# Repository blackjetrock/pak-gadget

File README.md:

# pak-gadget
Psion Organiser II datapak replacement using RP2040

Code for a replacement Psion datapak that uses the RP2040 to create a datapak image that is interfaced using one of the datapak slots in the Organiser.
The gadget has an SD slot that can hold .opk files which are presented to the organiser as a datapak. There's a small OLED display and buttons so the image can be selected. The pak gadget can also present a rampak and data can be stored on the ram pak. That can then be saved to SD card using the menu system.
Power is USB as the datapak interface does not have a permanent power supply.

There are two versions:

Breakout pak-gadget
===================

A 'breakout' pak-gadget which is a T shaped PCB that plugs in to the datapak slot and has the display and buttons facing forwards. This is quite large.

Pak Sized pak-gadget
====================

This is a pak-gadget that fits in the form factor of a datapak in the slot in the organiser. It has a smaller OLED display and buttons that both face towards the back of the organiser. Power is still USB. When disconnected from power the organiser cover should fit in the closed position. The gadget can be wired in to the internal power supply of the organiser.On older PCB designs this requires an external transistor and a wire to the gadget. The later designs have that on the gadget PCB and require two wires.

Operation
=========

The pak gadget plugs in to either datapack slot on a Psion Organiser 2. It can be powered by the USB socket on the PCB, or it can be wired in to the 
internal supply of the organiser. A transistor is needed to switch the battery voltage on to the gadget when the LCD controller is turned on. When wired in 
the USB connection MUST NOT be used. A later revision of the PCB (untested as yet) has the extra transistor needed for internal power on the PCB.

The gadget runs in a tight loop when emulating a datapack in order to operate at the speeds needed to interact with the Psion, which means it cannot handle a 
menu while emulating.

There are four buttons on the gadget. The left most button breaks the gadget out of its tight loop and starts a menu. UP and DOWN are the rightmost two 
buttons. The button second from left is an OK button.

The code reads a file called config.txt from the SD card when it starts up. At the moment this just sets the .OPK image that will initially be used.
pack header bytes are passed through from the OPk file to the organiser unchanged, apart from the size byte. The pak gadget can only support pack images up to 
and including 128K so the size byte is altered to be no larger than 128K.

Menu options
============

List
----
This lists the .OPK files on the SD card. Selecting a file loads it into the gadget RAM buffer ready to emulate it when the menu is exited.

Write
-----
This writes the current RAM data to a file on the SD card. This enables a pak gadget that has been used as a RAM pack to save the data on SD card so that 
it can be loaded back in later. When power is removed the RAM b uffer is lost so this is the only way to have non volatile storage with the pak gadget.

The files are written with the name:
paknnnnn.opk

where nnnnn is an increasing number for each file saved. The pak gadget checks for the last nnnnn used by a file on the SD card and picks the next 
highest number for each file write.

Blank
-----
This clears the RAM buffer and sets the pak gadget up as a blank pack which can then be sized and used as a RAM pack.

Exit
----
This exits the menu and enters the emulation loop so that the pak gadget will look like a datapack again. While in the menu system the gadget does not emulate a pack.

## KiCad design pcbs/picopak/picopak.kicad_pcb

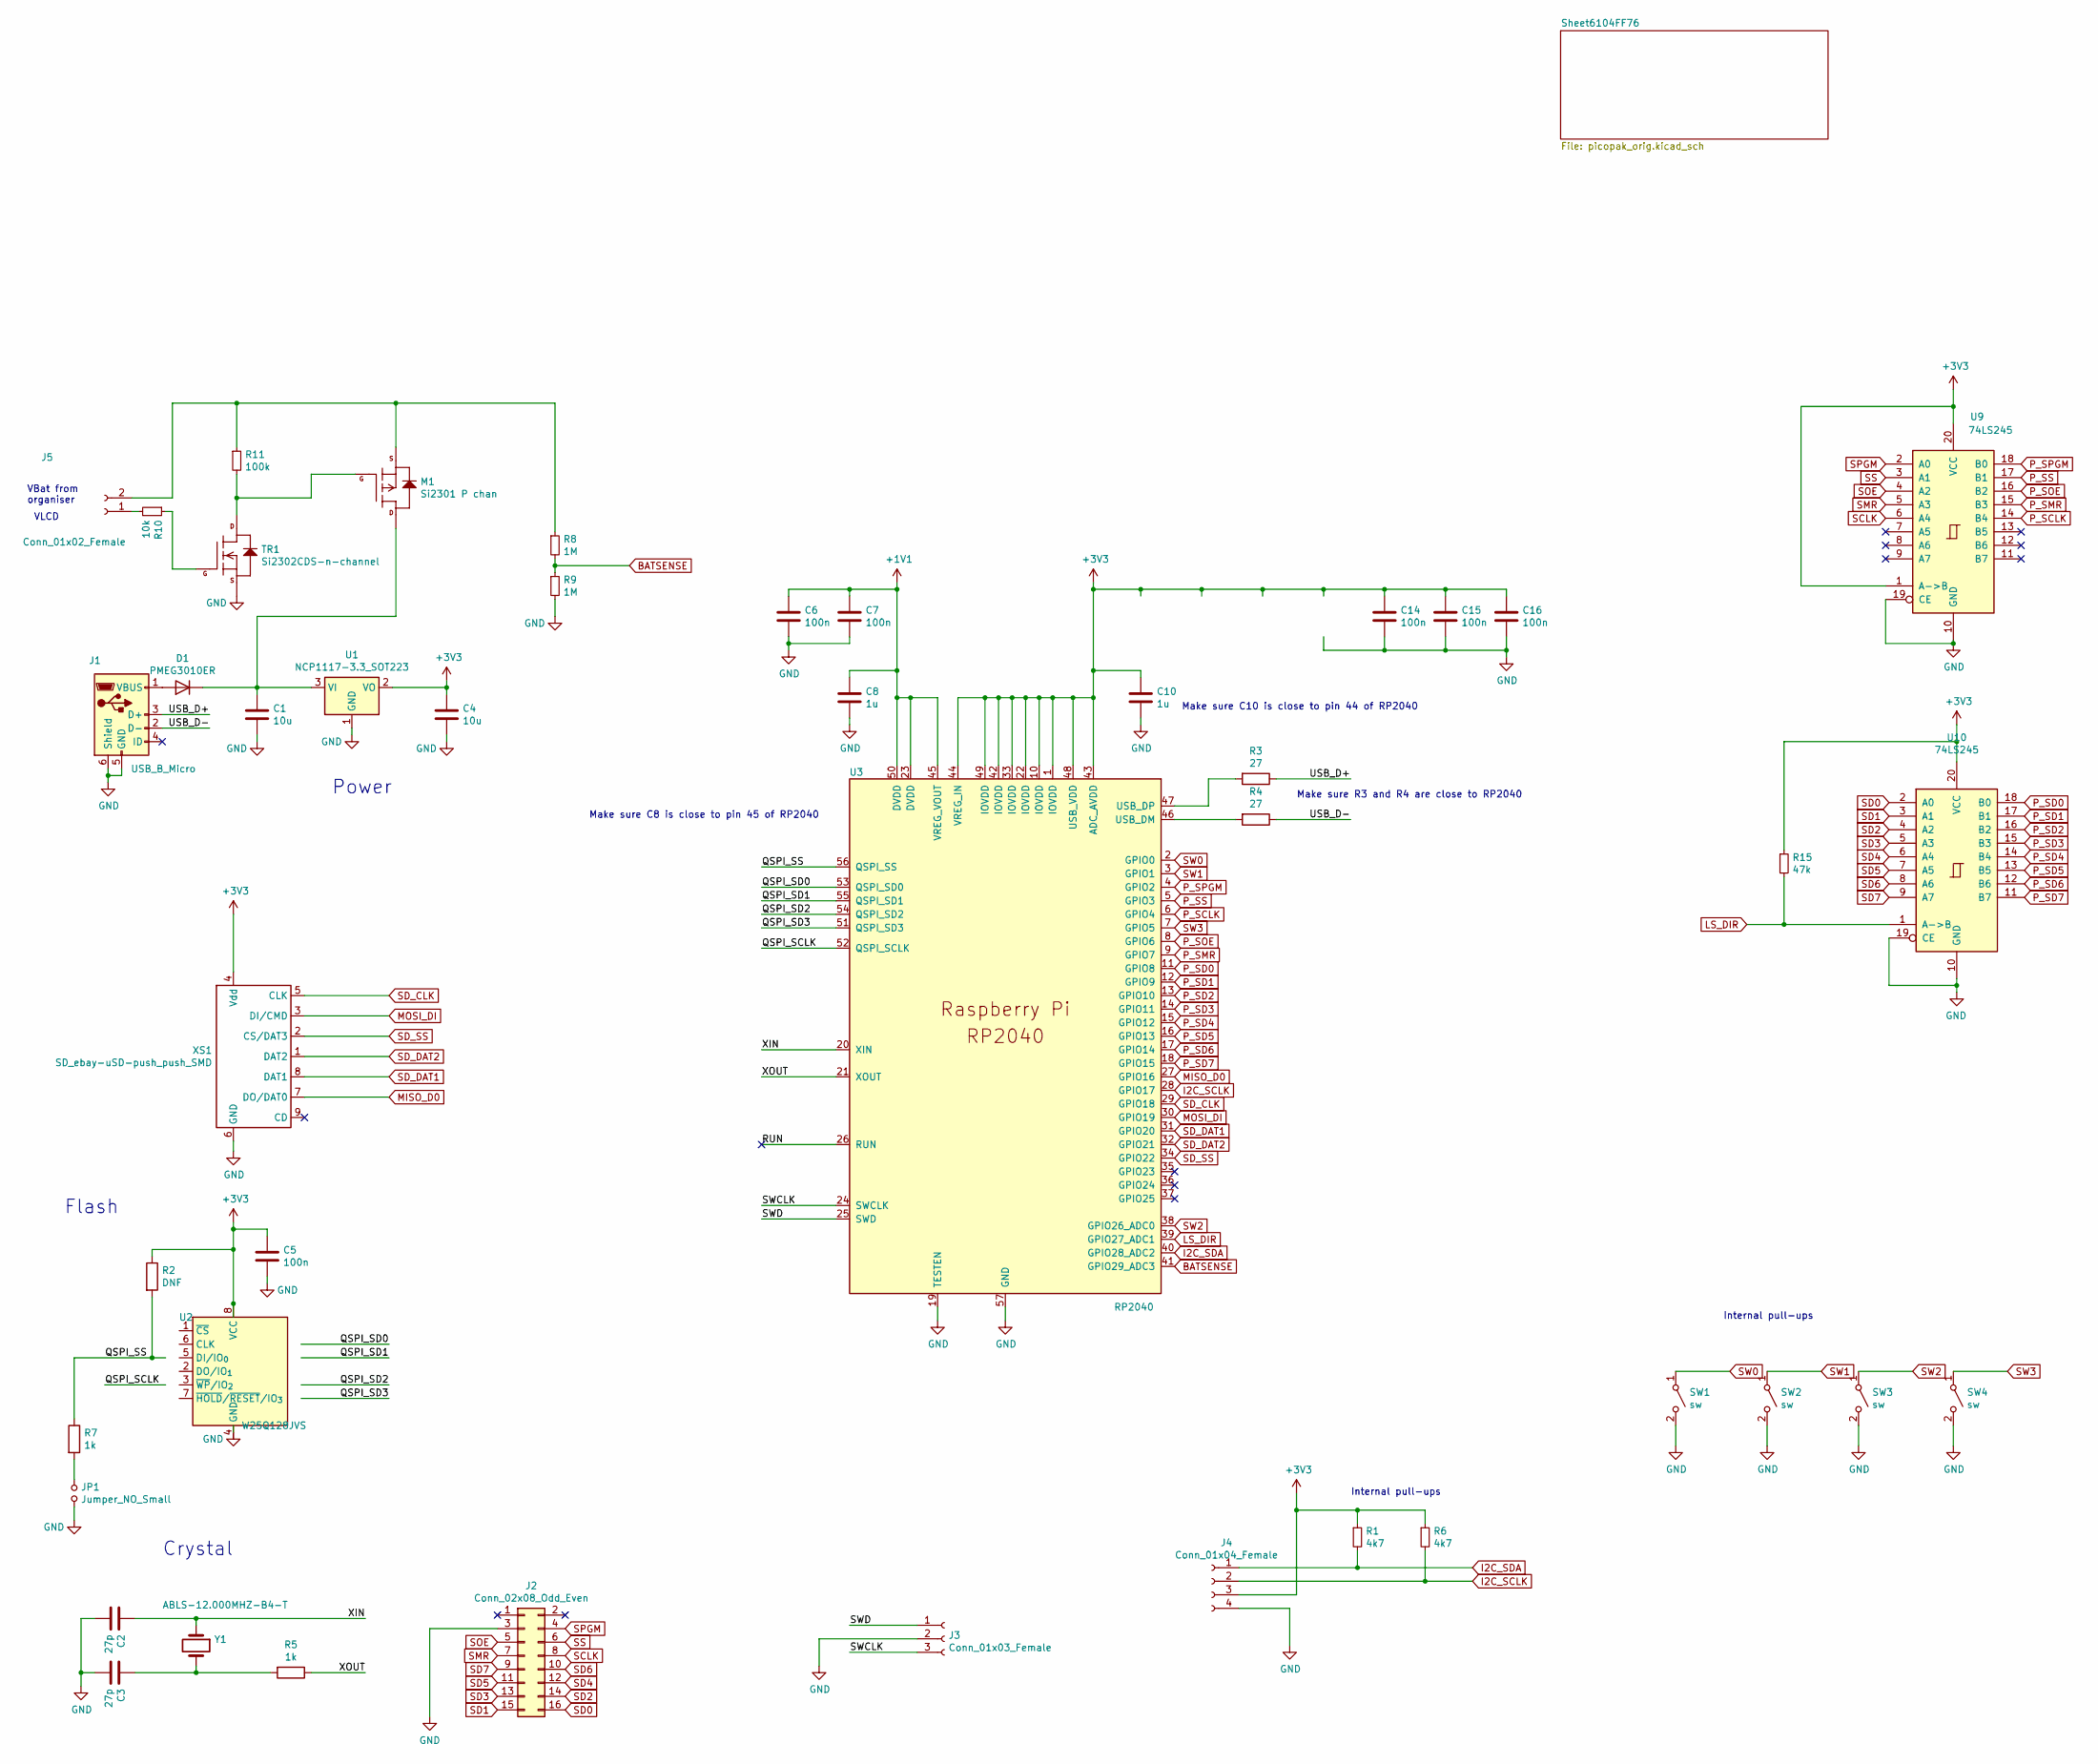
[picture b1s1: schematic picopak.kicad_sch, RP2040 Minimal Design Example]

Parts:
C1: 10u; C_0805_2012Metric
C2, C3: 27p; C_0402_1005Metric
C4: 10u; C_0402_1005Metric
C5, C6, C7, C14, C15, C16: 100n; C_0402_1005Metric
C8, C10: 1u; C_0402_1005Metric
D1: PMEG3010ER; D_SOD-123
J1: USB_B_Micro; USB_Micro-B_Amphenol_10103594-0001LF_Horizontal_modified
J2: Conn_02x08_Odd_Even; Psion_datapak_2x08_P2.54mm_Horizontal
J3: Conn_01x03_Female; PinHeader_1x03_P1.00mm_Vertical_SMD_Pin1Left
J4: Conn_01x04_Female; OLED_SMALL
J5: Conn_01x02_Female; PinHeader_1x02_P1.00mm_Vertical_SMD_Pin1Left
JP1: Jumper_NO_Small; SolderJumper-2_P1.3mm_Open_Pad1.0x1.5mm
M1: Si2301 P chan; SOT-23
R1, R6: 4k7; C_0402_1005Metric
R2: DNF; C_0402_1005Metric
R3, R4: 27; C_0402_1005Metric
R5, R7: 1k; C_0402_1005Metric
R8, R9: 1M; C_0402_1005Metric
R10: 10k; C_0402_1005Metric
R11: 100k; C_0402_1005Metric
R15: 47k; C_0402_1005Metric
SW1, SW2, SW3, SW4: sw; SW_Push_1P1T_NO_Vertical_Wuerth_434133025816
TR1: Si2302CDS-n-channel; SOT-23
U1: NCP1117-3.3_SOT223; SOT-223-3_TabPin2
U2: W25Q128JVS; SOIC-8_5.23x5.23mm_P1.27mm
U3: RP2040; RP2040-QFN-56-no_holes
U9, U10: 74LS245; TSSOP-20_4.4x6.5mm_P0.65mm
XS1: SD_ebay-uSD-push_push_SMD; Conn_uSDcard
Y1: ABLS-12.000MHZ-B4-T; Crystal_SMD_3225-4Pin_3.2x2.5mm_HandSoldering

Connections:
+1V1: C6.1, C7.1, C8.1, U3.23 (DVDD), U3.45 (VREG_VOUT), U3.50 (DVDD)
+3V3: C4.1, C5.1, C10.1, C14.1, C15.1, C16.1, J4.3, R1.1, R2.1, R6.1, R15.1, U1.2 (VO), U2.8 (VCC), U3.1 (IOVDD), U3.10 (IOVDD), U3.22 (IOVDD), U3.33 (IOVDD), U3.42 (IOVDD), U3.43 (ADC_AVDD), U3.44 (VREG_IN), U3.48 (USB_VDD), U3.49 (IOVDD), U9.1 (A->B), U9.20 (VCC), U10.20 (VCC), XS1.4 (Vdd)
/QSPI_SCLK: U2.6 (CLK), U3.52 (QSPI_SCLK)
/QSPI_SD0: U2.5 (DI/IO_{0}), U3.53 (QSPI_SD0)
/QSPI_SD1: U2.2 (DO/IO_{1}), U3.55 (QSPI_SD1)
/QSPI_SD2: U2.3 (~WP/IO_{2}), U3.54 (QSPI_SD2)
/QSPI_SD3: U2.7 (~HOLD/~RESET/IO_{3}), U3.51 (QSPI_SD3)
/QSPI_SS: R2.2, R7.1, U2.1 (~CS), U3.56 (QSPI_SS)
/SWCLK: J3.3, U3.24 (SWCLK)
/SWD: J3.1, U3.25 (SWD)
/USB_D+: J1.3 (D+), R3.1
/USB_D-: J1.2 (D-), R4.1
/XIN: C2.1, U3.20 (XIN), Y1.1
/XOUT: R5.1, U3.21 (XOUT)
BATSENSE: R8.2, R9.1, U3.41 (GPIO29_ADC3)
GND: C1.2, C2.2, C3.2, C4.2, C5.2, C6.2, C7.2, C8.2, C10.2, C14.2, C15.2, C16.2, J1.5 (GND), J1.6 (Shield), J2.3, J3.2, J4.4, JP1.2, R9.2, SW1.2 (B), SW2.2 (B), SW3.2 (B), SW4.2 (B), TR1.2 (S), U1.1 (GND), U2.4 (GND), U3.19 (TESTEN), U3.57 (GND), U9.10 (GND), U9.19 (CE), U10.10 (GND), U10.19 (CE), XS1.6 (GND)
I2C_SCLK: J4.2, R6.2, U3.28 (GPIO17)
I2C_SDA: J4.1, R1.2, U3.40 (GPIO28_ADC2)
LS_DIR: R15.2, U3.39 (GPIO27_ADC1), U10.1 (A->B)
MISO_D0: U3.27 (GPIO16), XS1.7 (DO/DAT0)
MOSI_DI: U3.30 (GPIO19), XS1.3 (DI/CMD)
unnamed: C1.1, D1.1 (K), M1.3 (D), U1.3 (VI)
unnamed: C3.1, R5.2, Y1.2
unnamed: D1.2 (A), J1.1 (VBUS)
unnamed: J5.1, R10.2
unnamed: J5.2, M1.2 (S), R8.1, R11.1
unnamed: JP1.1, R7.2
unnamed: M1.1 (G), R11.2, TR1.3 (D)
unnamed: R3.2, U3.47 (USB_DP)
unnamed: R4.2, U3.46 (USB_DM)
unnamed: R10.1, TR1.1 (G)
P_SCLK: U3.6 (GPIO4), U9.14 (B4)
P_SD0: U3.11 (GPIO8), U10.18 (B0)
P_SD1: U3.12 (GPIO9), U10.17 (B1)
P_SD2: U3.13 (GPIO10), U10.16 (B2)
P_SD3: U3.14 (GPIO11), U10.15 (B3)
P_SD4: U3.15 (GPIO12), U10.14 (B4)
P_SD5: U3.16 (GPIO13), U10.13 (B5)
P_SD6: U3.17 (GPIO14), U10.12 (B6)
P_SD7: U3.18 (GPIO15), U10.11 (B7)
P_SMR: U3.9 (GPIO7), U9.15 (B3)
P_SOE: U3.8 (GPIO6), U9.16 (B2)
P_SPGM: U3.4 (GPIO2), U9.18 (B0)
P_SS: U3.5 (GPIO3), U9.17 (B1)
SCLK: J2.8, U9.6 (A4)
SD0: J2.16, U10.2 (A0)
SD1: J2.15, U10.3 (A1)
SD2: J2.14, U10.4 (A2)
SD3: J2.13, U10.5 (A3)
SD4: J2.12, U10.6 (A4)
SD5: J2.11, U10.7 (A5)
SD6: J2.10, U10.8 (A6)
SD7: J2.9, U10.9 (A7)
SD_CLK: U3.29 (GPIO18), XS1.5 (CLK)
SD_DAT1: U3.31 (GPIO20), XS1.8 (DAT1)
SD_DAT2: U3.32 (GPIO21), XS1.1 (DAT2)
SD_SS: U3.34 (GPIO22), XS1.2 (CS/DAT3)
SMR: J2.7, U9.5 (A3)
SOE: J2.5, U9.4 (A2)
SPGM: J2.4, U9.2 (A0)
SS: J2.6, U9.3 (A1)
SW0: SW1.1 (A), U3.2 (GPIO0)
SW1: SW2.1 (A), U3.3 (GPIO1)
SW2: SW3.1 (A), U3.38 (GPIO26_ADC0)
SW3: SW4.1 (A), U3.7 (GPIO5)

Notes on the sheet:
Make sure R3 and R4 are close to RP2040
VLCD
Internal pull-ups
Make sure C10 is close to pin 44 of RP2040
Power
VBat from organiser
Crystal
Make sure C8 is close to pin 45 of RP2040
Flash

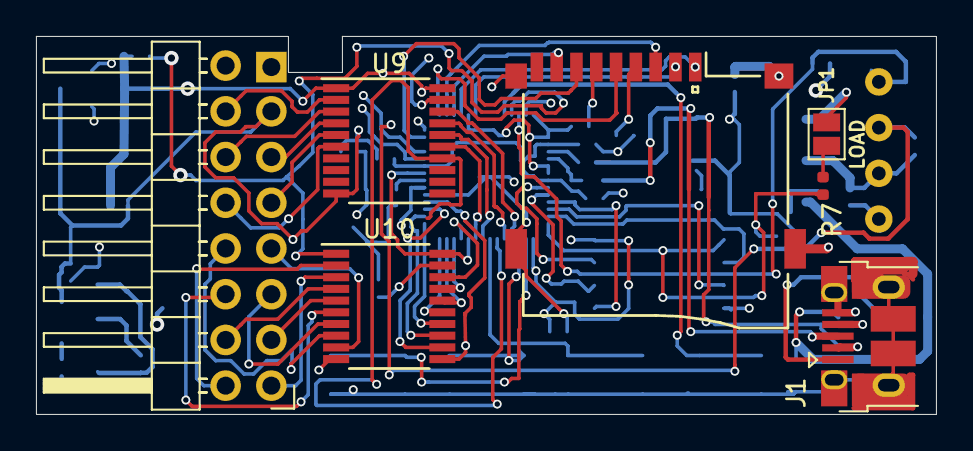
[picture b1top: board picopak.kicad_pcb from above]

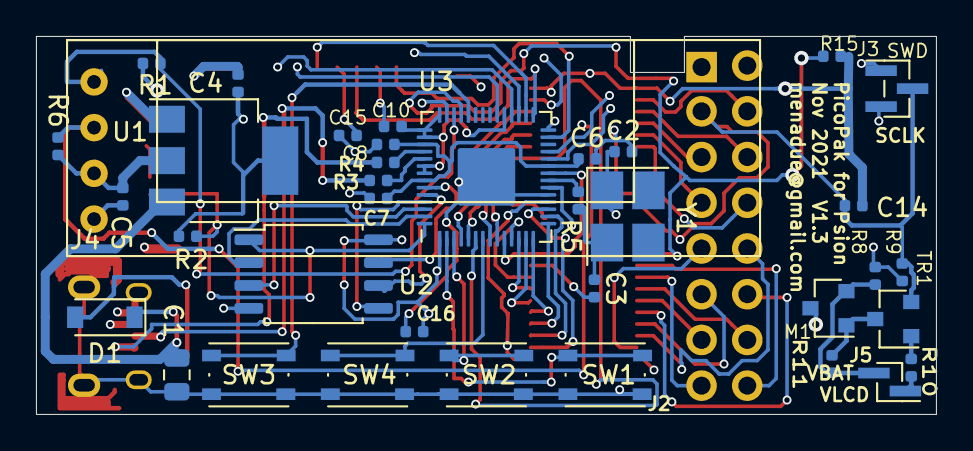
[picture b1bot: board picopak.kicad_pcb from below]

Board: 4 copper layers, 50.0 x 21.0 mm, 44 parts (37 on the bottom side), 65 nets.

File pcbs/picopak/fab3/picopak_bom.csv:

Comment,Designator,Footprint
Si2301 P chan,M1,SOT-23
100k,R11,C_0402_1005Metric
10k,R10,C_0402_1005Metric
1M,"R9,R8",C_0402_1005Metric
Si2302CDS-n-channel,TR1,SOT-23
Conn_01x02_Female,J5,PinHeader_1x02_P1.00mm_Vertical_SMD_Pin1Left
PMEG3010ER,D1,D_SOD-123
1k,"R7,R5",C_0402_1005Metric
Jumper_NO_Small,JP1,SolderJumper-2_P1.3mm_Open_Pad1.0x1.5mm
Conn_01x03_Female,J3,PinHeader_1x03_P1.00mm_Vertical_SMD_Pin1Left
10u,C4,C_0402_1005Metric
27p,"C2,C3",C_0402_1005Metric
100n,"C5,C6,C7,C14,C15,C16",C_0402_1005Metric
1u,"C8,C10",C_0402_1005Metric
4k7,"R6,R1",C_0402_1005Metric
47k,R15,C_0402_1005Metric
74LS245,"U9,U10",TSSOP-20_4.4x6.5mm_P0.65mm
RP2040,U3,RP2040-QFN-56-no_holes
ABLS-12.000MHZ-B4-T,Y1,Crystal_SMD_3225-4Pin_3.2x2.5mm_HandSoldering
Conn_01x04_Female,J4,OLED_SMALL
sw,"SW4,SW3,SW2,SW1",SW_Push_1P1T_NO_Vertical_Wuerth_434133025816
SD_ebay-uSD-push_push_SMD,XS1,Conn_uSDcard
Conn_02x08_Odd_Even,J2,Psion_datapak_2x08_P2.54mm_Horizontal
USB_B_Micro,J1,USB_Micro-B_Amphenol_10103594-0001LF_Horizontal_modified
W25Q128JVS,U2,SOIC-8_5.23x5.23mm_P1.27mm
NCP1117-3.3_SOT223,U1,SOT-223-3_TabPin2
27,"R4,R3",C_0402_1005Metric
DNF,R2,C_0402_1005Metric
10u,C1,C_0805_2012Metric

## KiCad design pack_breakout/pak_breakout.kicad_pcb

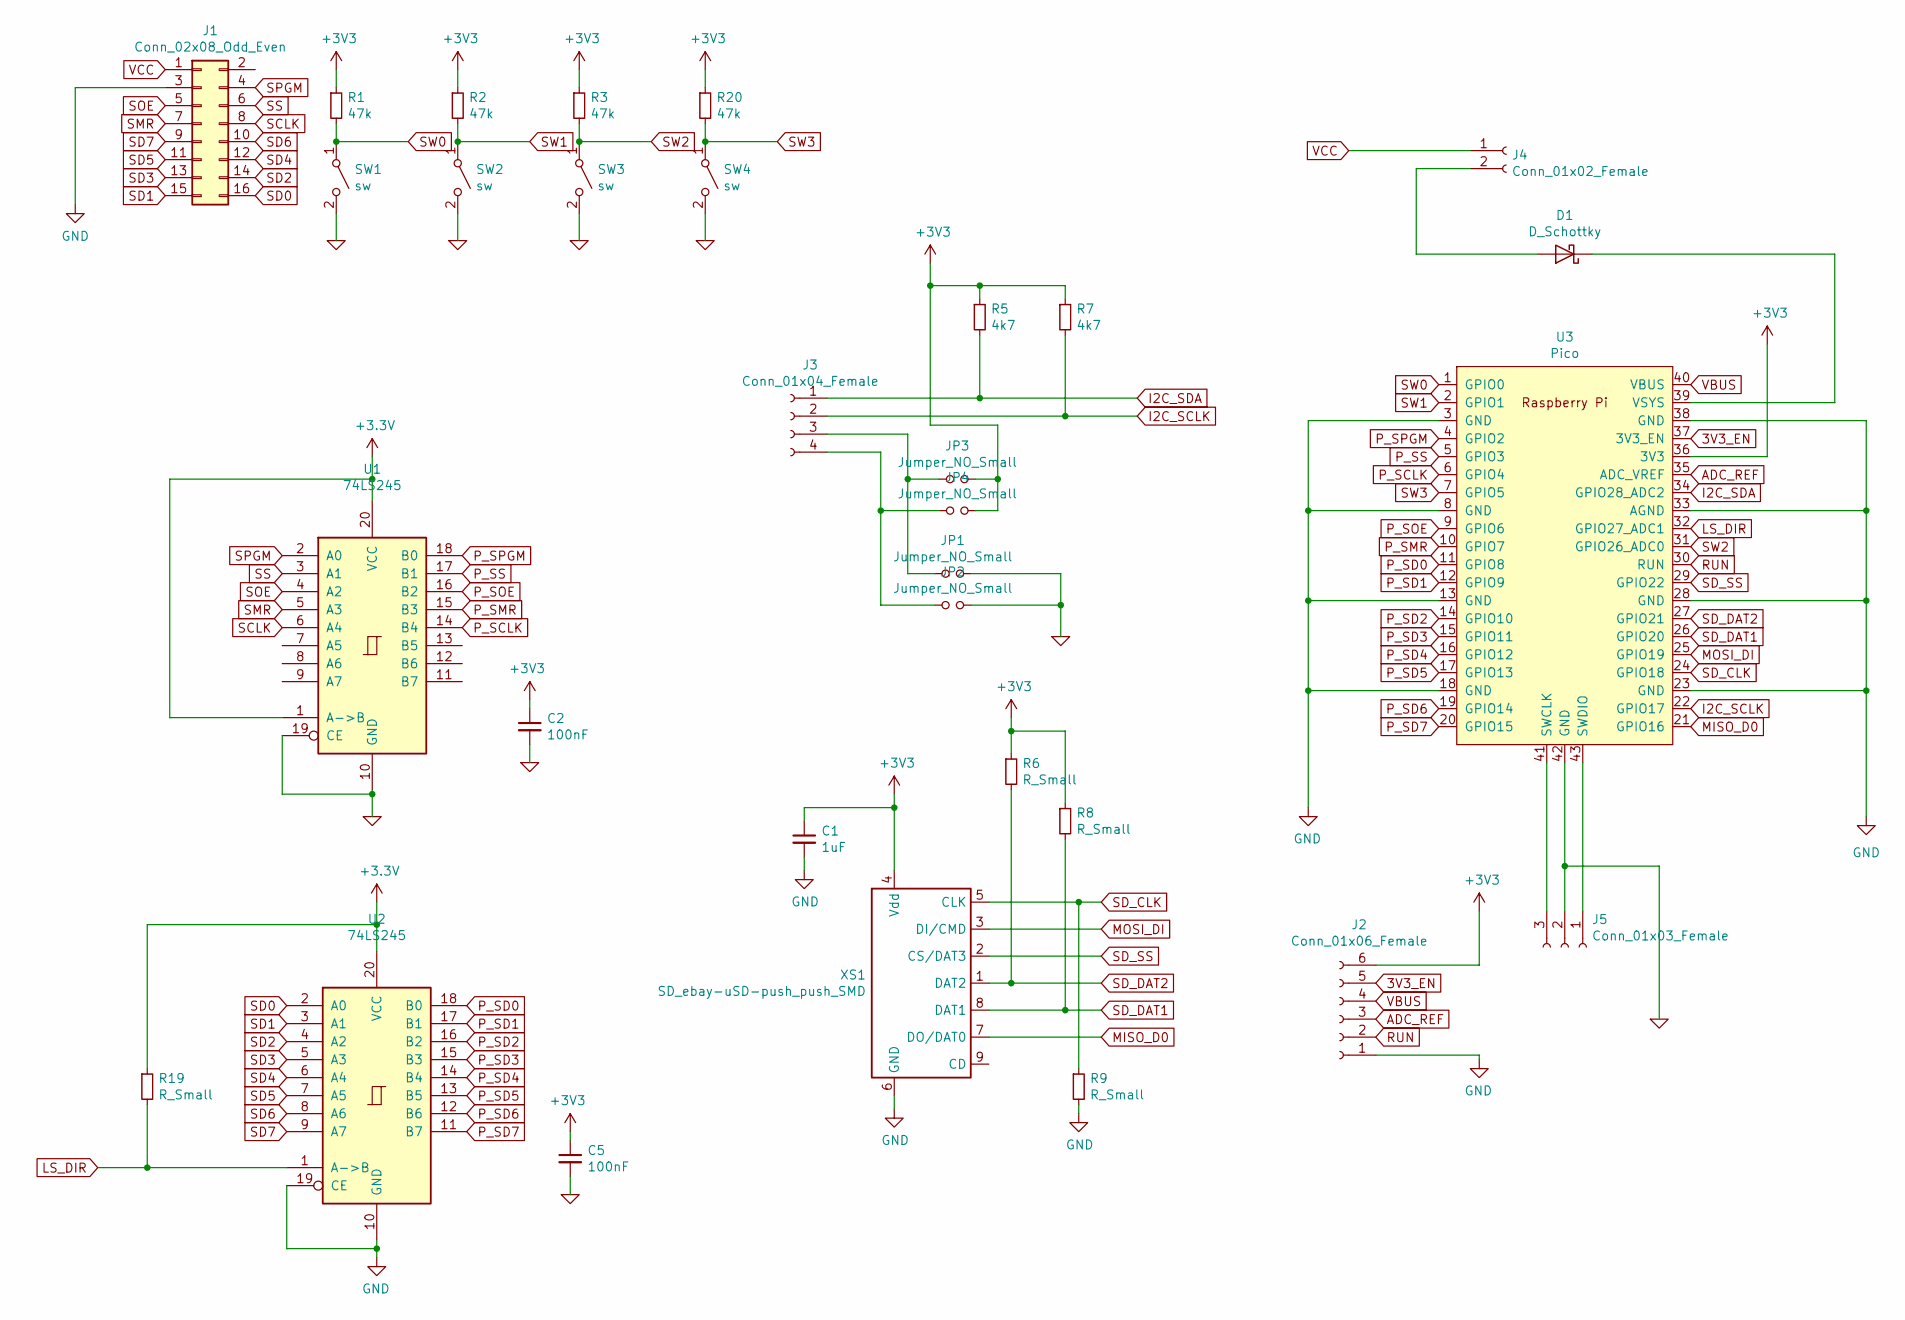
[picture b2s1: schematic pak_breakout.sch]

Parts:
C1: 1uF; C_0805_2012Metric
C2, C5: 100nF; C_0805_2012Metric
D1: D_Schottky; D_SOD-123
J1: Conn_02x08_Odd_Even; Psion_datapak_2x08_P2.54mm_Horizontal
J2: Conn_01x06_Female; PinSocket_1x06_P2.54mm_Vertical
J3: Conn_01x04_Female; PinHeader_1x04_P2.54mm_Vertical
J4: Conn_01x02_Female; PinHeader_1x02_P2.54mm_Vertical
J5: Conn_01x03_Female; PinHeader_1x03_P2.54mm_Vertical
JP1, JP2, JP3, JP4: Jumper_NO_Small; SolderJumper-2_P1.3mm_Open_RoundedPad1.0x1.5mm
R1, R2, R3, R20: 47k; R_0805_2012Metric
R5, R7: 4k7; R_0805_2012Metric
R6, R8, R9, R19: R_Small; R_0805_2012Metric
SW1, SW2, SW3, SW4: sw; SW_PUSH-12mm
U1, U2: 74LS245; SOIC-20W_7.5x12.8mm_P1.27mm
U3: Pico; RPi_Pico_SMD_TH
XS1: SD_ebay-uSD-push_push_SMD; Conn_uSDcard

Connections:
3V3_EN: J2.5, U3.37 (3V3_EN)
ADC_REF: J2.3, U3.35 (ADC_VREF)
GND: C1.2, C2.2, C5.2, J1.3, J2.1, J5.2, JP1.2, JP2.2, R9.2, SW1.2 (B), SW2.2 (B), SW3.2 (B), SW4.2 (B), U1.10 (GND), U1.19 (CE), U2.10 (GND), U2.19 (CE), U3.3 (GND), U3.8 (GND), U3.13 (GND), U3.18 (GND), U3.23 (GND), U3.28 (GND), U3.33 (AGND), U3.38 (GND), U3.42 (GND), XS1.6 (GND)
I2C_SCLK: J3.2, R7.2, U3.22 (GPIO17)
I2C_SDA: J3.1, R5.2, U3.34 (GPIO28_ADC2)
LS_DIR: R19.2, U2.1 (A->B), U3.32 (GPIO27_ADC1)
MISO_D0: U3.21 (GPIO16), XS1.7 (DO/DAT0)
MOSI_DI: U3.25 (GPIO19), XS1.3 (DI/CMD)
unnamed: D1.1 (K), U3.39 (VSYS)
unnamed: D1.2 (A), J4.2
unnamed: J3.3, JP1.1, JP3.1
unnamed: J3.4, JP2.1, JP4.1
unnamed: J5.1, U3.43 (SWDIO)
unnamed: J5.3, U3.41 (SWCLK)
P_SCLK: U1.14 (B4), U3.6 (GPIO4)
P_SD0: U2.18 (B0), U3.11 (GPIO8)
P_SD1: U2.17 (B1), U3.12 (GPIO9)
P_SD2: U2.16 (B2), U3.14 (GPIO10)
P_SD3: U2.15 (B3), U3.15 (GPIO11)
P_SD4: U2.14 (B4), U3.16 (GPIO12)
P_SD5: U2.13 (B5), U3.17 (GPIO13)
P_SD6: U2.12 (B6), U3.19 (GPIO14)
P_SD7: U2.11 (B7), U3.20 (GPIO15)
P_SMR: U1.15 (B3), U3.10 (GPIO7)
P_SOE: U1.16 (B2), U3.9 (GPIO6)
P_SPGM: U1.18 (B0), U3.4 (GPIO2)
P_SS: U1.17 (B1), U3.5 (GPIO3)
RUN: J2.2, U3.30 (RUN)
SCLK: J1.8, U1.6 (A4)
SD0: J1.16, U2.2 (A0)
SD1: J1.15, U2.3 (A1)
SD2: J1.14, U2.4 (A2)
SD3: J1.13, U2.5 (A3)
SD4: J1.12, U2.6 (A4)
SD5: J1.11, U2.7 (A5)
SD6: J1.10, U2.8 (A6)
SD7: J1.9, U2.9 (A7)
SD_CLK: R9.1, U3.24 (GPIO18), XS1.5 (CLK)
SD_DAT1: R8.2, U3.26 (GPIO20), XS1.8 (DAT1)
SD_DAT2: R6.2, U3.27 (GPIO21), XS1.1 (DAT2)
SD_SS: U3.29 (GPIO22), XS1.2 (CS/DAT3)
SMR: J1.7, U1.5 (A3)
SOE: J1.5, U1.4 (A2)
SPGM: J1.4, U1.2 (A0)
SS: J1.6, U1.3 (A1)
SW0: R1.2, SW1.1 (A), U3.1 (GPIO0)
SW1: R2.2, SW2.1 (A), U3.2 (GPIO1)
SW2: R3.2, SW3.1 (A), U3.31 (GPIO26_ADC0)
SW3: R20.2, SW4.1 (A), U3.7 (GPIO5)
VBUS: J2.4, U3.40 (VBUS)
VCC: J1.1, J4.1

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
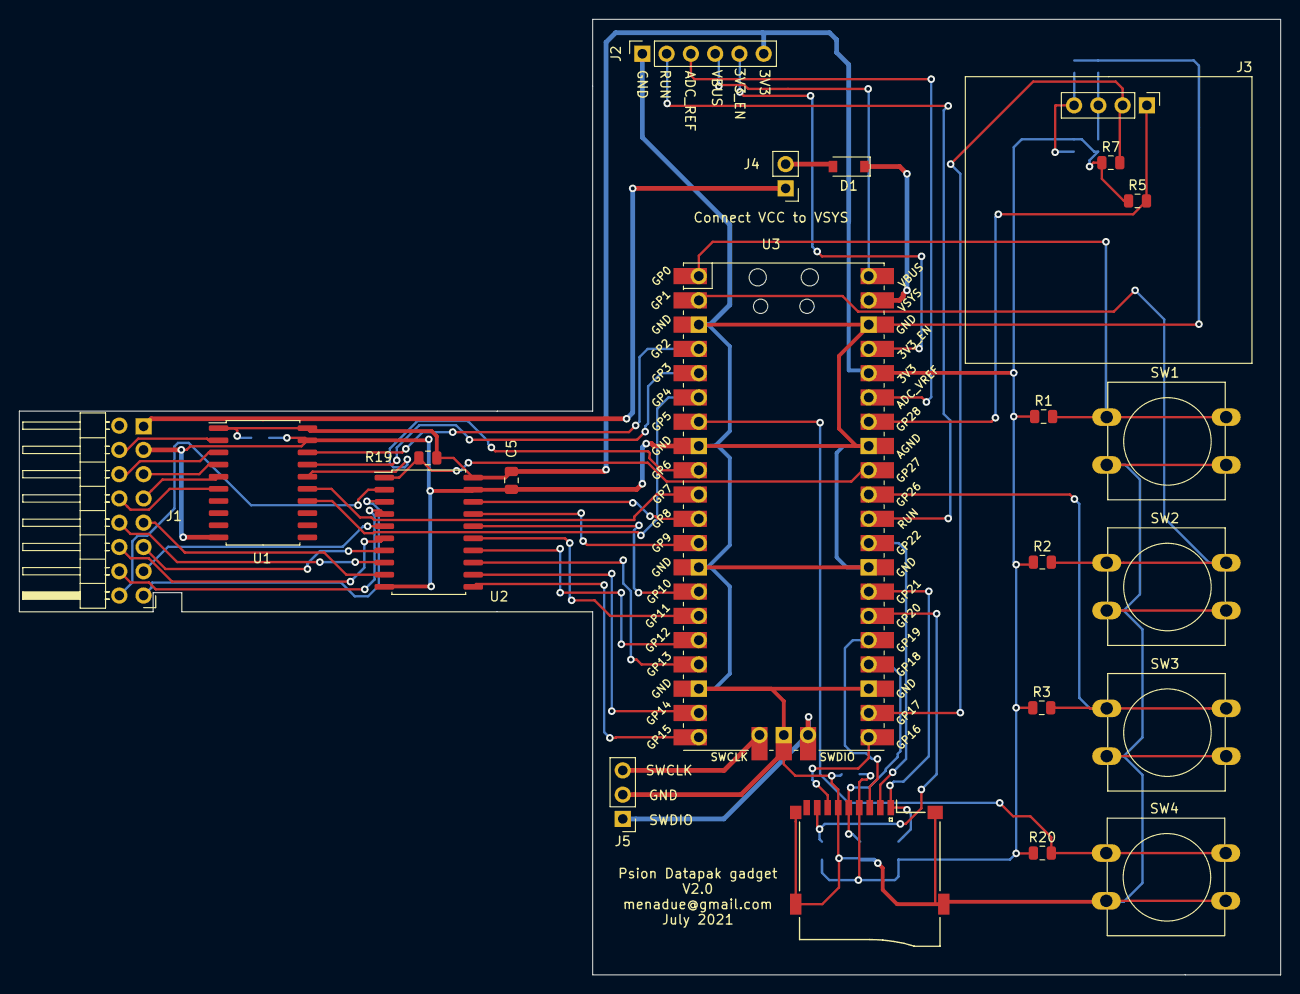
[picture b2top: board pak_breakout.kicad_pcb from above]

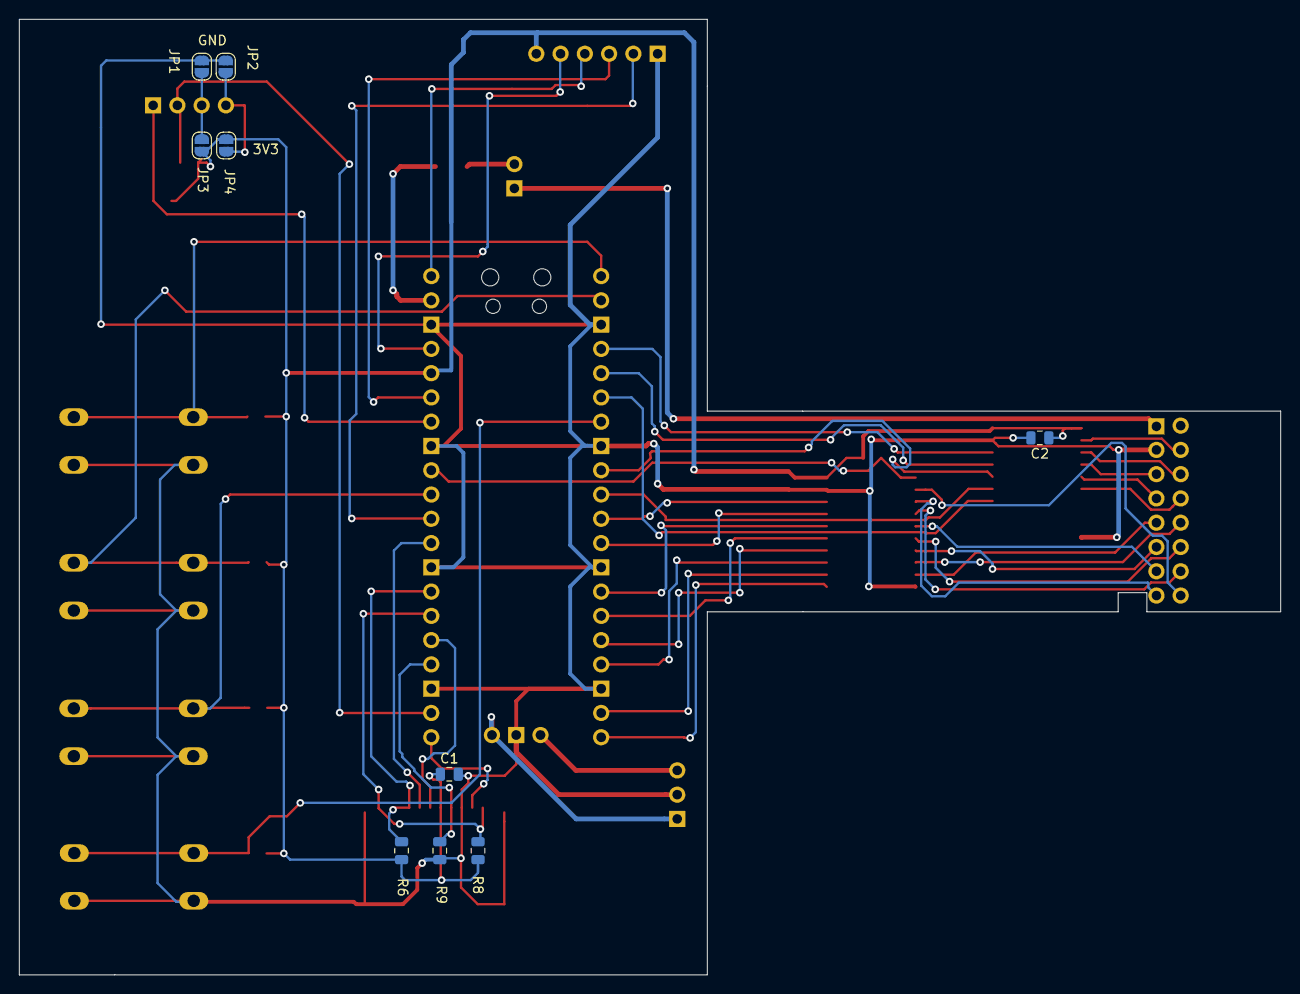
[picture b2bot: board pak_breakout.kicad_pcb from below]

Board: 2 copper layers, 132.0 x 100.0 mm, 31 parts (9 on the bottom side), 52 nets.

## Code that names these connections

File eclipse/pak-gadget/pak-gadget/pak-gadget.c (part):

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const int SLOT_SD6_PIN  = 14;
const int SLOT_SD7_PIN  = 15;

const int LS_DIR_PIN    = 27;

volatile int ss_count = 0;
volatile int soe_state = 1;
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  int data = 0;

  // As we are reading the bus, the direction line should be high
  gpio_put(LS_DIR_PIN, 1);
  
#if DIRECT_GPIO
  // Direct register access, as it's faster
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{
  // Drive level shifters to be driving Psion

  gpio_put(LS_DIR_PIN, 0);

#if DIRECT_GPIO
#if 0
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#endif
  // Drive level shifters to be driving Pico
  
  gpio_put(LS_DIR_PIN, 1);

}

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  // Get current output states
  states = sio_hw->gpio_out;

  // Our data has its LSB at GPIO8
  states &= 0xFFFF00FF;
  sio_hw->gpio_out = states | (dat <<8);
#else
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      // Read GPIO states
      ss     = gpio_get(SLOT_SS_PIN);
      sclk   = gpio_get(SLOT_SCLK_PIN);
      soe    = gpio_get(SLOT_SOE_PIN);
      smr    = gpio_get(SLOT_SMR_PIN);
      spgm   = gpio_get(SLOT_SPGM_PIN);
      
      //----------------------------------------------------------------------
      // SCLK handling
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  gpio_set_dir(SLOT_SPGM_PIN, GPIO_IN);

  // Drive data bus towards us
  gpio_init(LS_DIR_PIN);
  gpio_put(LS_DIR_PIN, 1);

  // LS_DIR is an output
  gpio_set_dir(LS_DIR_PIN, GPIO_OUT);
  set_bus_inputs();

#if USE_INTERRUPTS
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	  // Read GPIO states
	  ss     = gpio_get(SLOT_SS_PIN);
	  sclk   = gpio_get(SLOT_SCLK_PIN);
	  soe    = gpio_get(SLOT_SOE_PIN);
	  smr    = gpio_get(SLOT_SMR_PIN);
	  spgm   = gpio_get(SLOT_SPGM_PIN);
      
	  if( (last_ss == 1) && (ss == 0) )
	    {
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
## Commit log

2021-08-13 Initial check in of PCB files
2021-08-13 Added eclipse files for firmware
2021-08-13 Re-arranged directoruies, added fab1 errata for picopak
2021-08-16 Second PCB with errata fixed added
2021-08-27 Added config.txt file for startup
2021-08-27 Updates config file for startup
2021-09-01 Added RUN jumper for drag-drop upgrade, SWD pads moved
2021-09-05 Added errata for V1.1
2021-09-14 Updated errata
2021-09-16 Updated errata and updated code
2021-09-24 V1_2 PCB laid out
2021-11-13 Updates. Archive file for PCB
2021-11-19 Trace of failed boot added
2021-11-20 Now passes header through, up to 128K
2021-11-20 Tidied up
2026-03-16 "Update"
